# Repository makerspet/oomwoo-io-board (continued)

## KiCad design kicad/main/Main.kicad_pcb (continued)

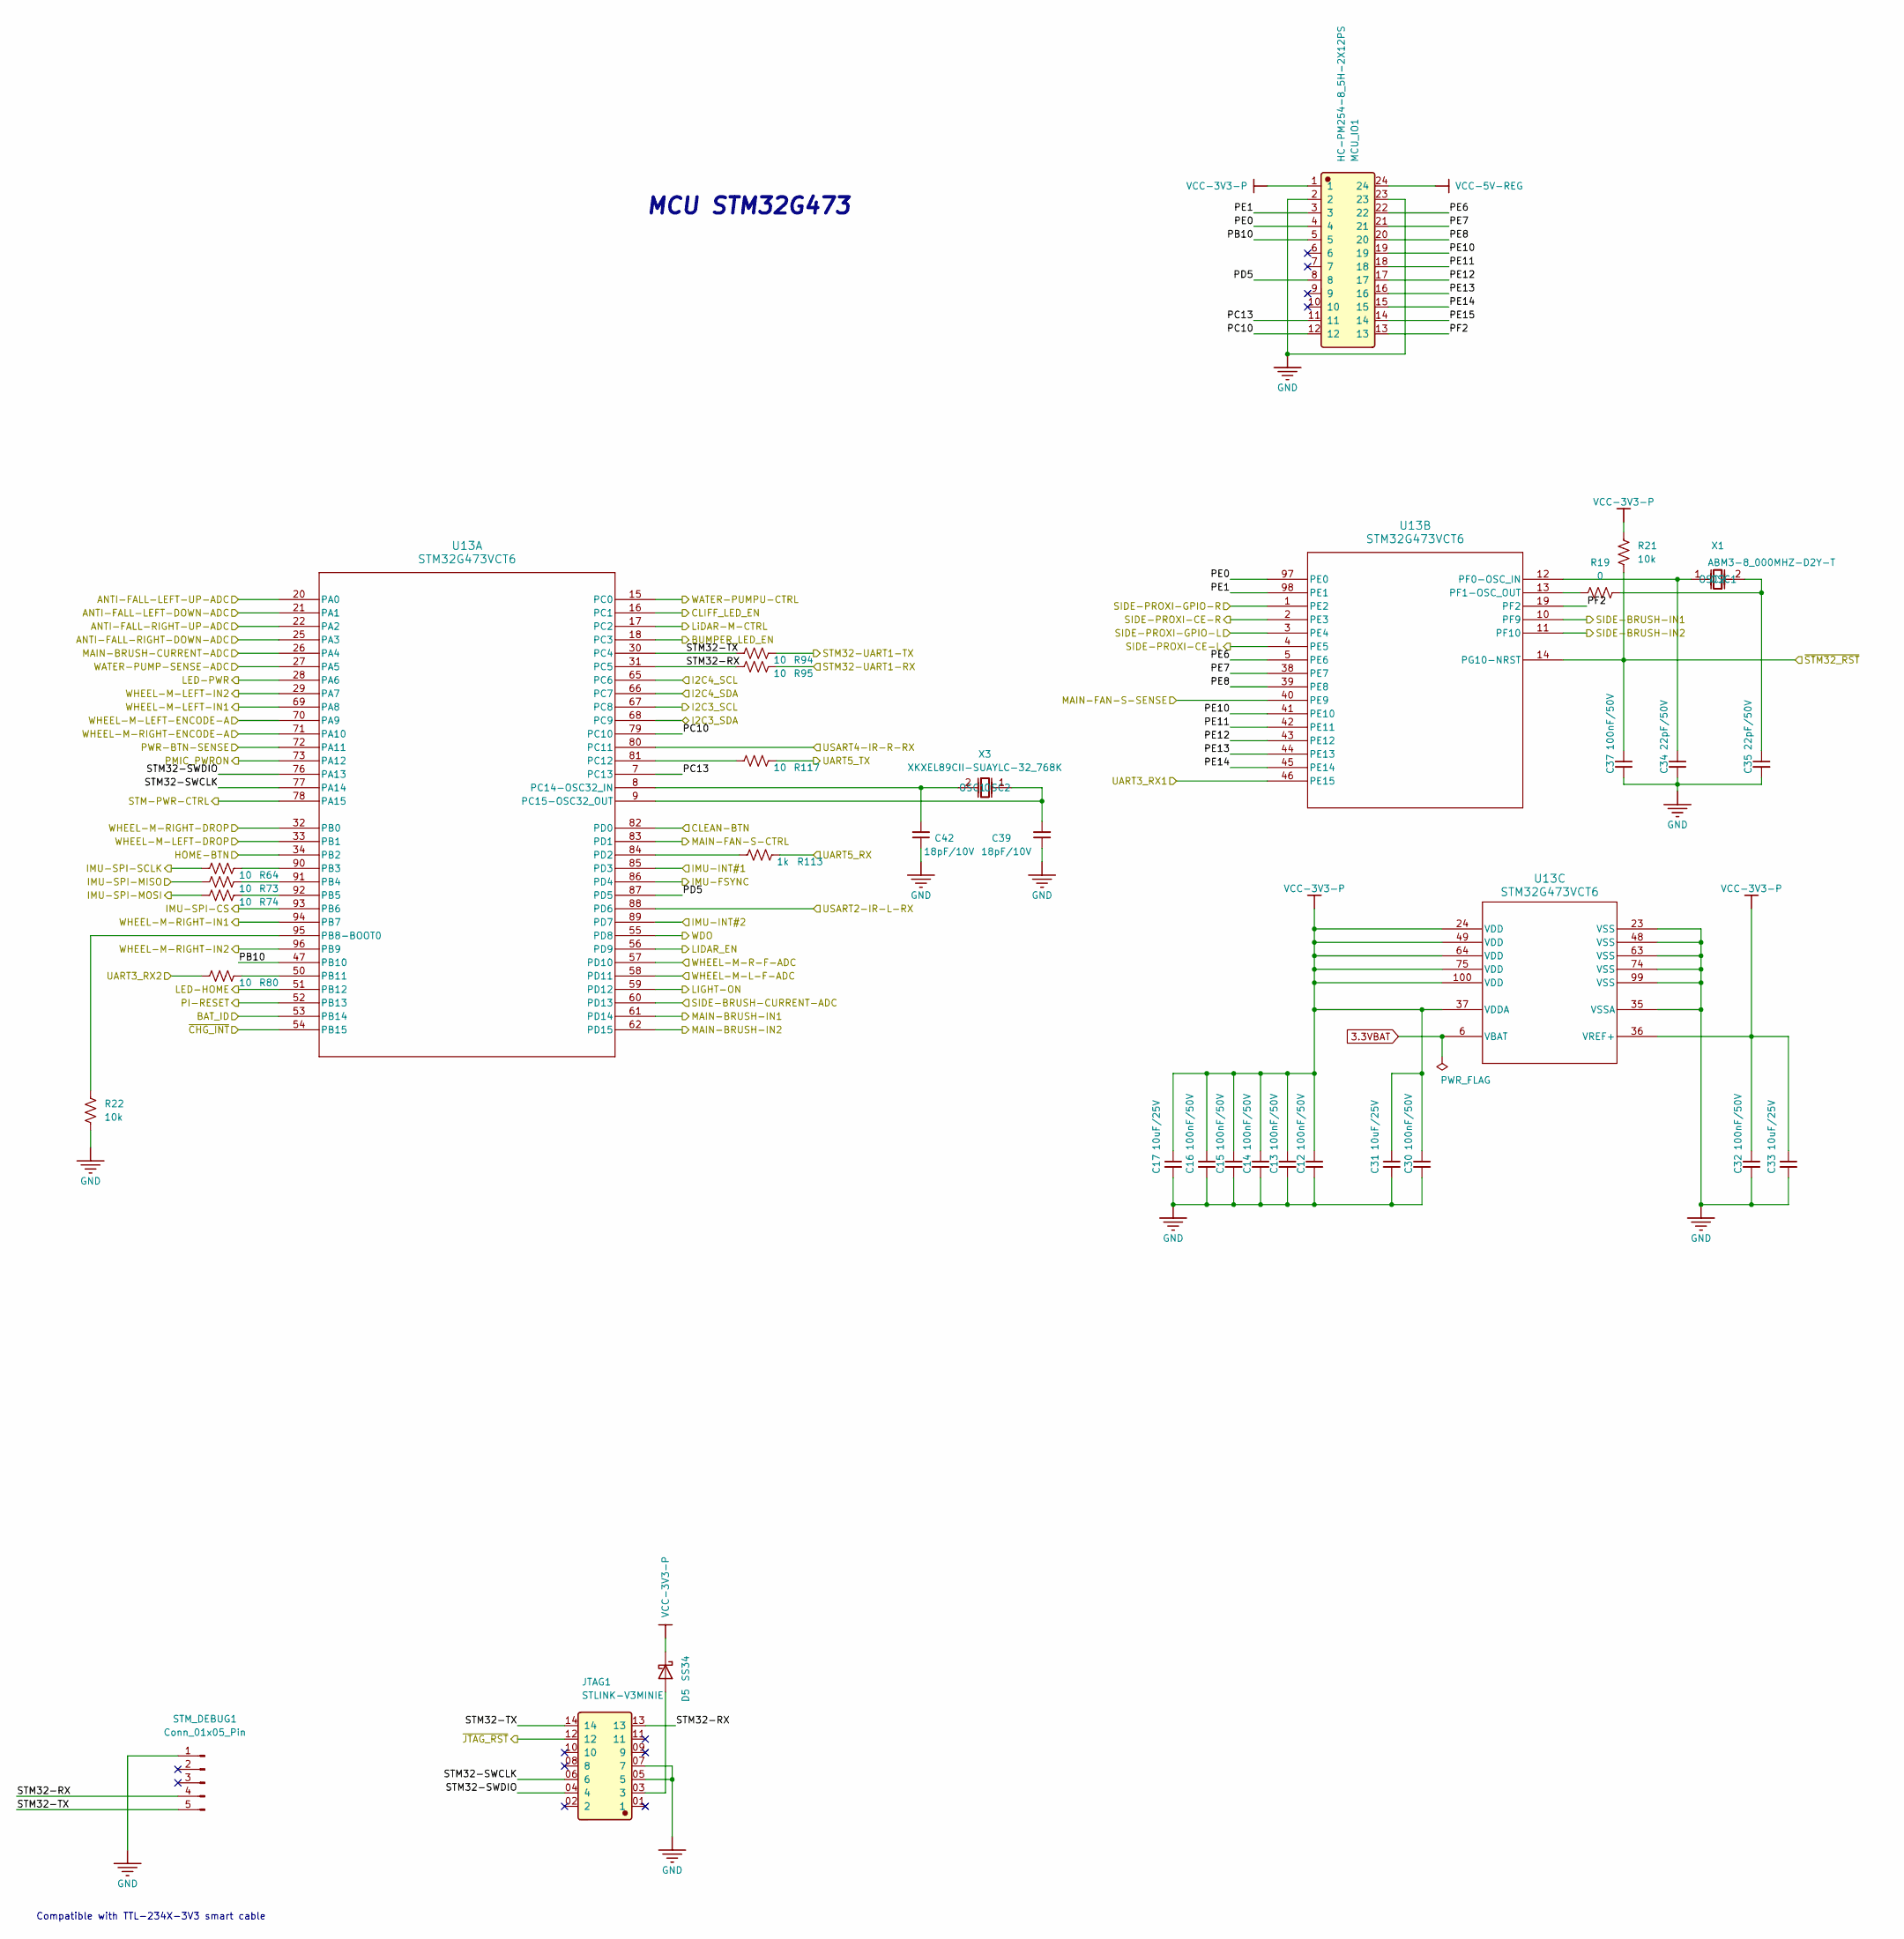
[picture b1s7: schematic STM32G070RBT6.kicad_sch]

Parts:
C12, C13, C14, C15, C16, C30, C32, C37: 100nF/50V; C_0603_1608Metric; LCSC C1591
C17, C31, C33: 10uF/25V; C_0603_1608Metric; LCSC C96446
C34, C35: 22pF/50V; C_0603_1608Metric
C39, C42: 18pF/10V; C_0603_1608Metric
D5: SS34; D_SMA; LCSC C22448055
JTAG1: STLINK-V3MINIE; FTSH-107-01-L-DV-K-A; Manufacturer Part FTSH-107-01-L-DV-K-A; LCSC C5563894
MCU_IO1: HC-PM254-8_5H-2X12PS; Manufacturer Part HC-PM254-8.5H-2x12PS; LCSC C22436159
R19: 0; R_0603_1608Metric
R21, R22: 10k; R_0603_1608Metric
R64, R73, R74, R80, R94, R95, R117: 10; R_0603_1608Metric
R113: 1k; R_0603_1608Metric
STM_DEBUG1: Conn_01x05_Pin; PinHeader_1x05_P2.54mm_Vertical; LCSC C42431835
U13: STM32G473VCT6; LQFP100-14x14mm; LCSC C730121
X1: ABM3-8_000MHZ-D2Y-T; Manufacturer Part ABM3-8.000MHZ-D2Y-T; LCSC C144380
X3: XKXEL89CII-SUAYLC-32_768K; Manufacturer Part XKXEL89CII-SUAYLC-32.768K; LCSC C18214309

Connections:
3.3VBAT: U13.6 (VBAT); also elsewhere on the board
/ANTI-FALL/ANTI-FALL-LEFT-DOWN-ADC: U13.21 (PA1); also elsewhere on the board
/ANTI-FALL/ANTI-FALL-LEFT-UP-ADC: U13.20 (PA0); also elsewhere on the board
/ANTI-FALL/ANTI-FALL-RIGHT-DOWN-ADC: U13.25 (PA3); also elsewhere on the board
/ANTI-FALL/ANTI-FALL-RIGHT-UP-ADC: U13.22 (PA2); also elsewhere on the board
/ANTI-FALL/BUMPER_LED_EN: U13.18 (PC3); also elsewhere on the board
/ANTI-FALL/CLIFF_LED_EN: U13.16 (PC1); also elsewhere on the board
/BATTERY-CHARGER/ID: U13.53 (PB14); also elsewhere on the board
/BATTERY-CHARGER/SCL: U13.67 (PC8); also elsewhere on the board
/BATTERY-CHARGER/SDA: U13.68 (PC9); also elsewhere on the board
/BATTERY-CHARGER/~INT: U13.54 (PB15); also elsewhere on the board
/BUTTON-LED/CLEAN-BTN: U13.82 (PD0); also elsewhere on the board
/BUTTON-LED/HOME-BTN: U13.34 (PB2); also elsewhere on the board
/BUTTON-LED/LED-HOME: U13.51 (PB12); also elsewhere on the board
/BUTTON-LED/LED-PWR: U13.28 (PA6); also elsewhere on the board
/CM5-GPIO/PMIC_EN: U13.52 (PB13); also elsewhere on the board
/CM5-GPIO/RUN_PG: U13.73 (PA12); also elsewhere on the board
/CM5-GPIO/UART2_RX: R94.2; also elsewhere on the board
/CM5-GPIO/UART2_TX: R95.2; also elsewhere on the board
/FRONT SENSORS/IR-F-RX1: U13.46 (PE15); also elsewhere on the board
/FRONT SENSORS/IR-F-RX2: R80.1; also elsewhere on the board
/FRONT SENSORS/LIGHT-ON: U13.59 (PD12); also elsewhere on the board
/IMU-CS: U13.93 (PB6); also elsewhere on the board
/IMU-FSYNC: U13.86 (PD4); also elsewhere on the board
/IMU-INT1: U13.85 (PD3); also elsewhere on the board
/IMU-INT2: U13.89 (PD7); also elsewhere on the board
/IMU-MISO: R73.1; also elsewhere on the board
/IMU-MOSI: R74.1; also elsewhere on the board
/IMU-SCLK: R64.1; also elsewhere on the board
/LiDAR/LIDAR_EN: U13.56 (PD9); also elsewhere on the board
/LiDAR/LiDAR-MOTOR-CTRL: U13.17 (PC2); also elsewhere on the board
/LiDAR/LiDAR-RXD: R113.2; also elsewhere on the board
/LiDAR/LiDAR-TXD: R117.2; also elsewhere on the board
/MAIN-BRUSH MOTOR/MAIN-BRUSH-CURRENT-ADC: U13.26 (PA4); also elsewhere on the board
/MAIN-BRUSH MOTOR/MAIN-BRUSH-IN1: U13.61 (PD14); also elsewhere on the board
/MAIN-BRUSH MOTOR/MAIN-BRUSH-IN2: U13.62 (PD15); also elsewhere on the board
/MAIN-FAN/MAIN-FAN-S-CTRL: U13.83 (PD1); also elsewhere on the board
/MAIN-FAN/MAIN-FAN-S-SENSE: U13.40 (PE9); also elsewhere on the board
/MCU-STM32/I2C4_SCL: U13.65 (PC6); also elsewhere on the board
/MCU-STM32/I2C4_SDA: U13.66 (PC7); also elsewhere on the board
/MCU-STM32/PB10: MCU_IO1.5, U13.47 (PB10)
/MCU-STM32/PC10: MCU_IO1.12, U13.79 (PC10)
/MCU-STM32/PC13: MCU_IO1.11, U13.7 (PC13)
/MCU-STM32/PD5: MCU_IO1.8, U13.87 (PD5)
/MCU-STM32/PE0: MCU_IO1.4, U13.97 (PE0)
/MCU-STM32/PE1: MCU_IO1.3, U13.98 (PE1)
/MCU-STM32/PE6: MCU_IO1.22, U13.5 (PE6)
/MCU-STM32/PE7: MCU_IO1.21, U13.38 (PE7)
/MCU-STM32/PE8: MCU_IO1.20, U13.39 (PE8)
/MCU-STM32/PE10: MCU_IO1.19, U13.41 (PE10)
/MCU-STM32/PE11: MCU_IO1.18, U13.42 (PE11)
/MCU-STM32/PE12: MCU_IO1.17, U13.43 (PE12)
/MCU-STM32/PE13: MCU_IO1.16, U13.44 (PE13)
/MCU-STM32/PE14: MCU_IO1.15, U13.45 (PE14)
/MCU-STM32/PE15: MCU_IO1.14
/MCU-STM32/PF2: MCU_IO1.13, U13.19 (PF2)
/MCU-STM32/PWR-BTN-SENSE: U13.72 (PA11); also elsewhere on the board
/MCU-STM32/SIDE-BRUSH-CURRENT-ADC: U13.60 (PD13); also elsewhere on the board
/MCU-STM32/SIDE-BRUSH-IN1: U13.10 (PF9); also elsewhere on the board
/MCU-STM32/SIDE-BRUSH-IN2: U13.11 (PF10); also elsewhere on the board
/MCU-STM32/SIDE-PROXI-CE-L: U13.4 (PE5); also elsewhere on the board
/MCU-STM32/SIDE-PROXI-CE-R: U13.2 (PE3); also elsewhere on the board
/MCU-STM32/SIDE-PROXI-GPIO-L: U13.3 (PE4); also elsewhere on the board
/MCU-STM32/SIDE-PROXI-GPIO-R: U13.1 (PE2); also elsewhere on the board
/MCU-STM32/STM32-RX: JTAG1.13, R95.1, STM_DEBUG1.4, U13.31 (PC5)
/MCU-STM32/STM32-SWCLK: JTAG1.06 (6), U13.77 (PA14)
/MCU-STM32/STM32-SWDIO: JTAG1.04 (4), U13.76 (PA13)
/MCU-STM32/STM32-TX: JTAG1.14, R94.1, STM_DEBUG1.5, U13.30 (PC4)
/MCU-STM32/STM-PWR-CTRL: U13.78 (PA15); also elsewhere on the board
/MCU-STM32/USART2-IR-L-RX: U13.88 (PD6); also elsewhere on the board
/MCU-STM32/USART4-IR-R-RX: U13.80 (PC11); also elsewhere on the board
/MCU-STM32/WATER-PUMP-SENSE-ADC: U13.27 (PA5); also elsewhere on the board
/MCU-STM32/WATER-PUMPU-CTRL: U13.15 (PC0); also elsewhere on the board
/MCU-STM32/WDO: U13.55 (PD8); also elsewhere on the board
/MCU-STM32/WHEEL-M-L-F-ADC: U13.58 (PD11); also elsewhere on the board
/MCU-STM32/WHEEL-M-LEFT-DROP: U13.33 (PB1); also elsewhere on the board
/MCU-STM32/WHEEL-M-LEFT-ENCODE-A: U13.70 (PA9); also elsewhere on the board
/MCU-STM32/WHEEL-M-LEFT-IN1: U13.69 (PA8); also elsewhere on the board
/MCU-STM32/WHEEL-M-LEFT-IN2: U13.29 (PA7); also elsewhere on the board
/MCU-STM32/WHEEL-M-R-F-ADC: U13.57 (PD10); also elsewhere on the board
/MCU-STM32/WHEEL-M-RIGHT-DROP: U13.32 (PB0); also elsewhere on the board
/MCU-STM32/WHEEL-M-RIGHT-ENCODE-A: U13.71 (PA10); also elsewhere on the board
/MCU-STM32/WHEEL-M-RIGHT-IN1: U13.94 (PB7); also elsewhere on the board
/MCU-STM32/WHEEL-M-RIGHT-IN2: U13.96 (PB9); also elsewhere on the board
/MCU-STM32/~JTAG_RST: JTAG1.12; also elsewhere on the board
/MCU-STM32/~STM32_RST: C37.1, R21.1, U13.14 (PG10-NRST); also elsewhere on the board
GND: C12.2, C13.2, C14.2, C15.2, C16.2, C17.2, C30.2, C31.2, C32.2, C33.2, C34.2, C35.2, C37.2, C39.1, C42.1, JTAG1.05 (5), JTAG1.07 (7), MCU_IO1.2, MCU_IO1.23, R22.1, STM_DEBUG1.1, U13.23 (VSS), U13.35 (VSSA), U13.48 (VSS), U13.63 (VSS), U13.74 (VSS), U13.99 (VSS); also elsewhere on the board
unnamed: D5.2 (A), JTAG1.03 (3)
unnamed: R64.2, U13.90 (PB3)
unnamed: R73.2, U13.91 (PB4)
unnamed: R74.2, U13.92 (PB5)
unnamed: R22.2, U13.95 (PB8-BOOT0)
unnamed: R80.2, U13.50 (PB11)
unnamed: R117.1, U13.81 (PC12)
unnamed: C42.2, U13.8 (PC14-OSC32_IN), X3.2 (OSC2)
unnamed: C39.2, U13.9 (PC15-OSC32_OUT), X3.1 (OSC1)
unnamed: R113.1, U13.84 (PD2)
unnamed: C34.1, U13.12 (PF0-OSC_IN), X1.1 (OSC1)
unnamed: R19.1, U13.13 (PF1-OSC_OUT)
unnamed: C35.1, R19.2, X1.2 (OSC2)
VCC-3V3-P: C12.1, C13.1, C14.1, C15.1, C16.1, C17.1, C30.1, C31.1, C32.1, C33.1, D5.1 (K), MCU_IO1.1, R21.2, U13.24 (VDD), U13.36 (VREF+), U13.37 (VDDA), U13.49 (VDD), U13.64 (VDD), U13.75 (VDD), U13.100 (VDD); also elsewhere on the board
VCC-5V-REG: MCU_IO1.24; also elsewhere on the board

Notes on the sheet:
Compatible with TTL-234X-3V3 smart cable
MCU STM32G473

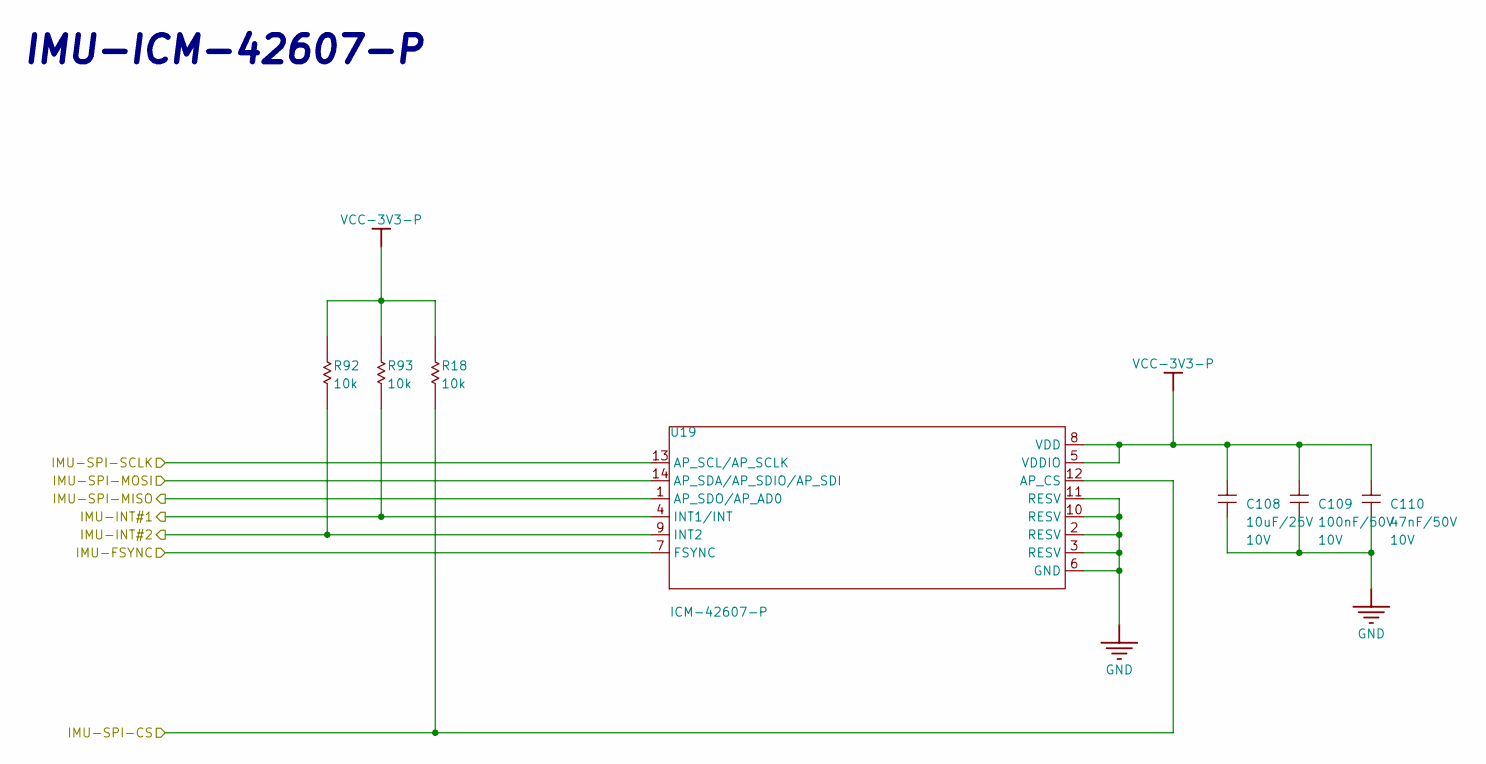
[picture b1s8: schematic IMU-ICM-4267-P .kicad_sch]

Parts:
C108: 10uF/25V; C_0603_1608Metric; VOLTAGERATE 10V; MANUFACTURINGPARTNUMBER *; LCSC C96446
C109: 100nF/50V; C_0603_1608Metric; VOLTAGERATE 10V; MANUFACTURINGPARTNUMBER *; LCSC C1591
C110: 47nF/50V; C_0603_1608Metric; VOLTAGERATE 10V; MANUFACTURINGPARTNUMBER *
R18, R92, R93: 10k; R_0603_1608Metric; VOLTAGERATE *; MANUFACTURINGPARTNUMBER *
U19: ICM-42607-P; VOLTAGERATE *; MANUFACTURINGPARTNUMBER *; LCSC C5129967

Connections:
/IMU-CS: R18.2, U19.12 (AP_CS); also elsewhere on the board
/IMU-FSYNC: U19.7 (FSYNC); also elsewhere on the board
/IMU-INT1: R93.2, U19.4 (INT1/INT); also elsewhere on the board
/IMU-INT2: R92.2, U19.9 (INT2); also elsewhere on the board
/IMU-MISO: U19.1 (AP_SDO/AP_AD0); also elsewhere on the board
/IMU-MOSI: U19.14 (AP_SDA/AP_SDIO/AP_SDI); also elsewhere on the board
/IMU-SCLK: U19.13 (AP_SCL/AP_SCLK); also elsewhere on the board
GND: C108.1, C109.1, C110.1, U19.2 (RESV), U19.3 (RESV), U19.6 (GND), U19.10 (RESV), U19.11 (RESV); also elsewhere on the board
VCC-3V3-P: C108.2, C109.2, C110.2, R18.1, R92.1, R93.1, U19.5 (VDDIO), U19.8 (VDD); also elsewhere on the board

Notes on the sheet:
IMU-ICM-42607-P

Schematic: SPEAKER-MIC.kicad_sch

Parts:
C5, C9, C10: 100nF/50V; C_0603_1608Metric; LCSC C1591
C11: 10uF/25V; C_0603_1608Metric; LCSC C96446
ED3: ESD5451N; ESD0402; PART REFERENCE ED7010; LCSC C5261080
ED4: ESD5451N; ESD0402; PART REFERENCE ED7011; LCSC C5261080
Q9: 2302V; Manufacturer Part 2302V; LCSC C7431443
R8, R13: 100k; R_0603_1608Metric
R9, R12: 0; R_0603_1608Metric
SPK1: ZX-ZH1_5-2PWT; Manufacturer Part ZX-ZH1.5-2PWT; LCSC C19272405
U9, U10: ICS-43434_C5656610; Manufacturer Part ICS-43434; LCSC C5656610
U11: MAX98357AETE_T; Manufacturer Part MAX98357AETE+T; LCSC C910544

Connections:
+3.3VP: R13.1; also elsewhere on the board
/CM5-GPIO/GPIO06: Q9.1 (G), R13.2; also elsewhere on the board
/CM5-GPIO/I2S_DOUT: U11.1 (DIN); also elsewhere on the board
/SPEAKER-MIC/BCLK: U9.4 (SCK), U10.4 (SCK), U11.16 (BCLK); also elsewhere on the board
/SPEAKER-MIC/DOUT: R8.1, U9.6 (SD), U10.6 (SD); also elsewhere on the board
/SPEAKER-MIC/LRCLK: U9.1 (WS), U10.1 (WS), U11.14 (LRCLK); also elsewhere on the board
GND: C5.2, C9.2, C10.2, C11.2, ED3.2, ED4.2, Q9.2 (S), R8.2, R12.1, SPK1.3, SPK1.4, U9.2 (LR), U9.3 (GND), U10.3 (GND), U11.3 (GND), U11.11 (GND), U11.15 (GND), U11.17 (EP); also elsewhere on the board
unnamed: Q9.3 (D), R9.1
unnamed: R12.2, U11.2 (GAIN_SLOT)
unnamed: ED3.1, SPK1.2, U11.10 (OUTN)
unnamed: ED4.1, SPK1.1, U11.9 (OUTP)
unnamed: R9.2, U11.4 (SD_MODE#)
VCC-3V3-P: C5.1, C9.1, U9.5 (VDD), U10.2 (LR), U10.5 (VDD); also elsewhere on the board
VCC-5V-REG: C10.1, C11.1, U11.7 (VDD), U11.8 (VDD); also elsewhere on the board

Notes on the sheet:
Microphone Input
RIGHT CHANNEL SELECT
SPEAKER MIC
LEFT CHANNEL SELECT
12dB

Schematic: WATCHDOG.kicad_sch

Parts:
C56: 100nF/50V; C_0603_1608Metric; Part Description 0.1uF 10% 16V Ceramic Capacitor X7R 040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; LCSC C1591
R135: 100k; R_0603_1608Metric
U2: TPS3828-33DBVR; Manufacturer Part TPS3828-33DBVR; LCSC C20032

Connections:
/MCU-STM32/WDO: U2.4 (WDI); also elsewhere on the board
/MCU-STM32/~JTAG_RST: R135.2, U2.3 (MR#); also elsewhere on the board
/MCU-STM32/~STM32_RST: U2.1 (RESET#); also elsewhere on the board
GND: C56.2, U2.2 (GND); also elsewhere on the board
VCC-3V3-P: C56.1, R135.1, U2.5 (VDD); also elsewhere on the board

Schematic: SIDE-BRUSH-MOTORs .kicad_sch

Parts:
C92: 100nF/50V; C_0603_1608Metric; VOLTAGERATE 50V; MANUFACTURINGPARTNUMBER *; LCSC C1591
C138: 10uF/25V; C_0603_1608Metric; LCSC C96446
D22: 1N4007; SOD123; VOLTAGERATE *; MANUFACTURINGPARTNUMBER *; LCSC C2892681
R55, R57: 100k; R_0603_1608Metric
R88: 0.2R/10W; R_2512_6332Metric; VOLTAGERATE *; MANUFACTURINGPARTNUMBER *; LCSC C5375488
R110: 10k; R_0603_1608Metric; VOLTAGERATE *; MANUFACTURINGPARTNUMBER *
SIDE_BRUSH1: ZX-ZH1_5-2PWT; Manufacturer Part ZX-ZH1.5-2PWT; LCSC C19272405
U18: DRV8870DDAR; VOLTAGERATE *; MANUFACTURINGPARTNUMBER *; LCSC C86590

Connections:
/MCU-STM32/SIDE-BRUSH-CURRENT-ADC: D22.1 (A), R110.1; also elsewhere on the board
/MCU-STM32/SIDE-BRUSH-IN1: R55.1, U18.3 (IN1); also elsewhere on the board
/MCU-STM32/SIDE-BRUSH-IN2: R57.1, U18.2 (IN2); also elsewhere on the board
GND: C92.1, C138.2, D22.2 (K), R55.2, R57.2, R88.1, SIDE_BRUSH1.3, SIDE_BRUSH1.4, U18.1 (GND), U18.9 (EP); also elsewhere on the board
unnamed: R88.2, R110.2, U18.7 (ISEN)
unnamed: SIDE_BRUSH1.1, U18.6 (OUT1)
unnamed: SIDE_BRUSH1.2, U18.8 (OUT2)
VCC-3V3-P: U18.4 (VREF); also elsewhere on the board
VM-VBAT: C92.2, C138.1, U18.5 (VM); also elsewhere on the board

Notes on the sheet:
SIDE-BRUSH MOTOR CONTROL

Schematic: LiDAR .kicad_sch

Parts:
C139: 10uF/25V; C_0603_1608Metric; LCSC C96446
D10: SS34; D_SMA; VOLTAGERATE *; MANUFACTURINGPARTNUMBER *; LCSC C22448055
Q20: AO3400; SOT23-3D; VOLTAGERATE *; MANUFACTURINGPARTNUMBER *; LCSC C20628874
R65: 1k; R_0603_1608Metric
R116, R118: 100k; R_0603_1608Metric; VOLTAGERATE *; MANUFACTURINGPARTNUMBER *
U3: HC-PM254-5_0H-2X4PS-02A; Manufacturer Part HC-PM254-5.0H-2x4PS-02A; LCSC C42163132

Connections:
/LiDAR/LIDAR_EN: R118.2, U3.6; also elsewhere on the board
/LiDAR/LiDAR-MOTOR-CTRL: Q20.1 (G), R116.2, U3.8; also elsewhere on the board
/LiDAR/LiDAR-RXD: R65.1; also elsewhere on the board
/LiDAR/LiDAR-TXD: U3.5; also elsewhere on the board
GND: C139.2, Q20.2 (S), R116.1, R118.1, U3.7; also elsewhere on the board
unnamed: D10.1 (A), Q20.3 (D), U3.4
unnamed: R65.2, U3.3
VCC-5V-REG: C139.1, D10.2 (K), U3.1, U3.2; also elsewhere on the board

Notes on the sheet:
LiDAR

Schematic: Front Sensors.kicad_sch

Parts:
C6, C19, C90, C91, C123: 10uF/25V; C_0603_1608Metric; LCSC C96446
IR-F1, IR-F2: ZX-ZH1_5-4PWT; Manufacturer Part ZX-ZH1.5-4PWT; LCSC C19272407
LIGHT1: ZX-ZH1_5-2PWT; Manufacturer Part ZX-ZH1.5-2PWT; LCSC C19272405
Q2: 2302V; Manufacturer Part 2302V; LCSC C7431443
R2, R7, R61, R62: 47k; R_0603_1608Metric
R5, R6: 2.2k; R_0603_1608Metric
R54: 100k; R_0603_1608Metric
VL-L1: ZX-ZH1_5-7PWT; Manufacturer Part ZX-ZH1.5-7PWT; LCSC C19272410
VL-R1: ZX-ZH1_5-7PWT; Manufacturer Part ZX-ZH1.5-7PWT; LCSC C19272410

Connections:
/CM5-GPIO/GPIO16: VL-R1.7; also elsewhere on the board
/CM5-GPIO/GPIO17: R2.1, VL-L1.3, VL-R1.3; also elsewhere on the board
/CM5-GPIO/GPIO25: R61.2, VL-L1.6; also elsewhere on the board
/CM5-GPIO/GPIO26: R62.2, VL-L1.7; also elsewhere on the board
/CM5-GPIO/GPIO27: R7.2, VL-R1.6; also elsewhere on the board
/CM5-GPIO/SCL1: R6.2, VL-L1.5, VL-R1.5; also elsewhere on the board
/CM5-GPIO/SDA1: R5.2, VL-L1.4, VL-R1.4; also elsewhere on the board
/FRONT SENSORS/IR-F-RX1: IR-F1.4; also elsewhere on the board
/FRONT SENSORS/IR-F-RX2: IR-F2.4; also elsewhere on the board
/FRONT SENSORS/LIGHT-ON: Q2.1 (G), R54.1; also elsewhere on the board
GND: C6.2, C19.2, C90.2, C91.2, C123.2, IR-F1.2, IR-F1.3, IR-F1.5, IR-F1.6, IR-F2.2, IR-F2.3, IR-F2.5, IR-F2.6, LIGHT1.3, LIGHT1.4, Q2.2 (S), R2.2, R54.2, VL-L1.2, VL-L1.8, VL-L1.9, VL-R1.2, VL-R1.8, VL-R1.9; also elsewhere on the board
unnamed: C6.1, VL-L1.1
unnamed: C123.1, LIGHT1.2, Q2.3 (D)
VCC-3V3-P: C19.1, C90.1, C91.1, IR-F1.1, IR-F2.1, LIGHT1.1, R5.1, R6.1, R7.1, R61.1, R62.1, VL-R1.1; also elsewhere on the board

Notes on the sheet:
SCL
VDD
LPn
I2C-RST
IR LIGHT
SDA
RECEIVER
INT
https://thepihut.com/products/850nm-ir-led-modules?srsltid=AfmBOorZ0hl4HylQHd5JbNfaA7bqJMbzrmY0bn7Mm12pD_mKEoiRE0nX
GND
2 IR RECEIVERS
2x VL53L7CX

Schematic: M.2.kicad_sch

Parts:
C45: 10uF/25V; C_0603_1608Metric; Manufacturer_Part_Number GRM21BR61H106KE43L; LCSC C96446
C50: 100nF/50V; C_0603_1608Metric; Manufacturer_Part_Number CL10B104KB8NNNC; LCSC C1591
J2: 1-2199119-5; TE_1-2199119-5; LCSC C574849
M2_ACT1: YLED0603B; Manufacturer Part YLED0603B; LCSC C19171394
MP1, MP2, MP3, MP4: M3 x 1.5mm; MountingHole_3.2mm_M3_Pad; PART-NUMBER 9774015360R
R79: 1k; R_0603_1608Metric
Y1: ASEK-32.768KHZ-LRT; XTAL_ASEK-32.768KHZ-LRT; PARTREV 01-11-22; LCSC C2650753

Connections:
/CM5-HIGHSPEED/PCIE_CLK_N: J2.53; also elsewhere on the board
/CM5-HIGHSPEED/PCIE_CLK_P: J2.55; also elsewhere on the board
/CM5-HIGHSPEED/PCIE_CLK_nREQ: J2.52; also elsewhere on the board
/CM5-HIGHSPEED/PCIE_RX_N: J2.43; also elsewhere on the board
/CM5-HIGHSPEED/PCIE_RX_P: J2.41; also elsewhere on the board
/CM5-HIGHSPEED/PCIE_TX_N: J2.49; also elsewhere on the board
/CM5-HIGHSPEED/PCIE_TX_P: J2.47; also elsewhere on the board
/CM5-HIGHSPEED/PCIE_nRST: J2.50; also elsewhere on the board
/CM5-HIGHSPEED/PCIE_nWAKE: J2.54; also elsewhere on the board
GND: C45.2, C50.2, J2.1, J2.3, J2.9, J2.15, J2.21, J2.27, J2.33, J2.39, J2.45, J2.51, J2.57, J2.71, J2.73, J2.75, J2.SH1 (SHIELD), J2.SH2 (SHIELD), MP1.1, MP2.1, MP3.1, MP4.1, Y1.2 (GND/CASE); also elsewhere on the board
unnamed: J2.10, M2_ACT1.2 (K)
unnamed: J2.68, Y1.3 (OUTPUT)
unnamed: M2_ACT1.1 (A), R79.2
VCC3V3_M2: C45.1, C50.1, J2.2, J2.4, J2.12, J2.14, J2.16, J2.18, J2.70, J2.72, J2.74, R79.1, Y1.1 (TRI-STATE), Y1.4 (VDD); also elsewhere on the board

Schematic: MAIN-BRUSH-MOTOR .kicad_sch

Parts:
C103: 100nF/50V; C_0603_1608Metric; VOLTAGERATE 50V; MANUFACTURINGPARTNUMBER *; LCSC C1591
C134: 10uF/25V; C_0603_1608Metric; LCSC C96446
MAIN_BRUSH1: ZX-ZH1_5-2PWT; Manufacturer Part ZX-ZH1.5-2PWT; LCSC C19272405
R3, R4: 100k; R_0603_1608Metric
R112: 0.2R/10W; R_2512_6332Metric; VOLTAGERATE *; MANUFACTURINGPARTNUMBER *; LCSC C5375488
U20: DRV8870DDAR; VOLTAGERATE *; MANUFACTURINGPARTNUMBER *; LCSC C86590

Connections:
/MAIN-BRUSH MOTOR/MAIN-BRUSH-CURRENT-ADC: R112.2, U20.7 (ISEN); also elsewhere on the board
/MAIN-BRUSH MOTOR/MAIN-BRUSH-IN1: R3.1, U20.3 (IN1); also elsewhere on the board
/MAIN-BRUSH MOTOR/MAIN-BRUSH-IN2: R4.1, U20.2 (IN2); also elsewhere on the board
GND: C103.1, C134.2, MAIN_BRUSH1.3, MAIN_BRUSH1.4, R3.2, R4.2, R112.1, U20.1 (GND), U20.9 (EP); also elsewhere on the board
unnamed: MAIN_BRUSH1.1, U20.6 (OUT1)
unnamed: MAIN_BRUSH1.2, U20.8 (OUT2)
VCC-3V3-P: U20.4 (VREF); also elsewhere on the board
VM-VBAT: C103.2, C134.1, U20.5 (VM); also elsewhere on the board

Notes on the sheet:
MAIN BUSH MOTOR CONTROL

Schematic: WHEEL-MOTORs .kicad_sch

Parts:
C84, C88: 100nF/50V; C_0603_1608Metric; VOLTAGERATE 50V; MANUFACTURINGPARTNUMBER *; LCSC C1591
C135, C136: 10uF/25V; C_0603_1608Metric; LCSC C96446
C142, C143: 100nF/50V; C_0603_1608Metric; Manufacturer_Part_Number CL10B104KB8NNNC; LCSC C1591
MOT_WHEEL_L1: ZX-ZH1_5-7PWT; Manufacturer Part ZX-ZH1.5-7PWT; LCSC C19272410
MOT_WHEEL_R1: ZX-ZH1_5-7PWT; Manufacturer Part ZX-ZH1.5-7PWT; LCSC C19272410
R11, R17, R20, R27: 100k; R_0603_1608Metric
R49, R50, R51, R52: 10k; R_0603_1608Metric
R83, R84: 0.2R/10W; R_2512_6332Metric; VOLTAGERATE *; MANUFACTURINGPARTNUMBER *; LCSC C5375488
U14, U15: DRV8870DDAR; VOLTAGERATE *; MANUFACTURINGPARTNUMBER *; LCSC C86590

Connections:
/MCU-STM32/WHEEL-M-L-F-ADC: R84.2, U15.7 (ISEN); also elsewhere on the board
/MCU-STM32/WHEEL-M-LEFT-DROP: MOT_WHEEL_L1.7, R50.2; also elsewhere on the board
/MCU-STM32/WHEEL-M-LEFT-ENCODE-A: MOT_WHEEL_L1.4, R52.2; also elsewhere on the board
/MCU-STM32/WHEEL-M-LEFT-IN1: R20.1, U15.3 (IN1); also elsewhere on the board
/MCU-STM32/WHEEL-M-LEFT-IN2: R27.1, U15.2 (IN2); also elsewhere on the board
/MCU-STM32/WHEEL-M-R-F-ADC: R83.2, U14.7 (ISEN); also elsewhere on the board
/MCU-STM32/WHEEL-M-RIGHT-DROP: MOT_WHEEL_R1.7, R49.2; also elsewhere on the board
/MCU-STM32/WHEEL-M-RIGHT-ENCODE-A: MOT_WHEEL_R1.4, R51.2; also elsewhere on the board
/MCU-STM32/WHEEL-M-RIGHT-IN1: R11.1, U14.3 (IN1); also elsewhere on the board
/MCU-STM32/WHEEL-M-RIGHT-IN2: R17.1, U14.2 (IN2); also elsewhere on the board
GND: C84.1, C88.1, C135.2, C136.2, C142.2, C143.2, MOT_WHEEL_L1.3, MOT_WHEEL_L1.6, MOT_WHEEL_L1.8, MOT_WHEEL_L1.9, MOT_WHEEL_R1.3, MOT_WHEEL_R1.6, MOT_WHEEL_R1.8, MOT_WHEEL_R1.9, R11.2, R17.2, R20.2, R27.2, R83.1, R84.1, U14.1 (GND), U14.9 (EP), U15.1 (GND), U15.9 (EP); also elsewhere on the board
unnamed: MOT_WHEEL_R1.1, U14.6 (OUT1)
unnamed: MOT_WHEEL_R1.2, U14.8 (OUT2)
unnamed: MOT_WHEEL_L1.1, U15.6 (OUT1)
unnamed: MOT_WHEEL_L1.2, U15.8 (OUT2)
VCC-3V3-P: C142.1, C143.1, MOT_WHEEL_L1.5, MOT_WHEEL_R1.5, R49.1, R50.1, R51.1, R52.1, U14.4 (VREF), U15.4 (VREF); also elsewhere on the board
VM-VBAT: C84.2, C88.2, C135.1, C136.1, U14.5 (VM), U15.5 (VM); also elsewhere on the board

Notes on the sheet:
WHEEL MOTOR CONTROL

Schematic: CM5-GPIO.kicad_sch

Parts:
BOOT1: Conn_01x02_Pin; PinHeader_1x02_P2.54mm_Vertical; LCSC C32713268
C1, C2, C4: 100nF/50V; C_0603_1608Metric; Part Description 0.1uF 10% 16V Ceramic Capacitor X7R 040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; LCSC C1591
C3: 10uF/25V; C_0603_1608Metric; Part Description 10uF 10% 10V Ceramic Capacitor X7R 0805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; LCSC C96446
CM_ACT1: YLED0603B; Manufacturer Part YLED0603B; LCSC C19171394
CM_PWR1: YLED0603B; Manufacturer Part YLED0603B; LCSC C19171394
CONSOLE1: Conn_01x05_Pin; PinHeader_1x05_P2.54mm_Vertical; LCSC C42431835
H1: PM254-2-06-S-8_5; Manufacturer Part PM254-2-06-S-8.5; LCSC C3975151
Module1: ComputeModule5-CM5; Raspberry-Pi-5-Compute-Module; Part Description 100 Position Connector Receptacle, Cent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; LCSC 2X C6932320
Q10: 2302V; Manufacturer Part 2302V; LCSC C7431443
R82, R85: 1k; R_0603_1608Metric
R142: 10k; R_0603_1608Metric
SDCARD2: 1040310811; Manufacturer Part 1040310811; LCSC C585350
U6: RT9742GGJ5; Manufacturer Part RT9742GGJ5; LCSC C250547

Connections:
+3.3VP: C1.1, Module1.78 (GPIO_VREF(1.8v/3.3v_Input)), Module1.84 (+3.3v_(Output)), Module1.86 (+3.3v_(Output)), R82.1, R85.1, R142.1, U6.5 (VIN); also elsewhere on the board
/CAMERA/CAM_GPIO0: Module1.100 (CAM_GPIO1); also elsewhere on the board
/CAMERA/CAM_GPIO1: Module1.97 (CAM_GPIO0); also elsewhere on the board
/CAMERA/ID_SC: Module1.35 (ID_SC); also elsewhere on the board
/CAMERA/ID_SD: Module1.36 (ID_SD); also elsewhere on the board
/CAMERA/SCL0: Module1.80 (SCL0); also elsewhere on the board
/CAMERA/SDA0: Module1.82 (SDA0); also elsewhere on the board
/CM5-GPIO/CONSOLE_RXD: CONSOLE1.4, Module1.51 (GPIO15)
/CM5-GPIO/CONSOLE_TXD: CONSOLE1.5, Module1.55 (GPIO14)
/CM5-GPIO/GPIO06: Module1.30 (GPIO6); also elsewhere on the board
/CM5-GPIO/GPIO7: H1.2, Module1.37 (GPIO7)
/CM5-GPIO/GPIO8: H1.1, Module1.39 (GPIO8)
/CM5-GPIO/GPIO9: H1.4, Module1.40 (GPIO9)
/CM5-GPIO/GPIO10: H1.3, Module1.44 (GPIO10)
/CM5-GPIO/GPIO11: H1.6, Module1.38 (GPIO11)
/CM5-GPIO/GPIO12: H1.9, Module1.31 (GPIO12)
/CM5-GPIO/GPIO13: H1.10, Module1.28 (GPIO13)
/CM5-GPIO/GPIO16: Module1.29 (GPIO16); also elsewhere on the board
/CM5-GPIO/GPIO17: Module1.50 (GPIO17); also elsewhere on the board
/CM5-GPIO/GPIO22: H1.5, Module1.46 (GPIO22)
/CM5-GPIO/GPIO23: H1.8, Module1.47 (GPIO23)
/CM5-GPIO/GPIO24: H1.7, Module1.45 (GPIO24)
/CM5-GPIO/GPIO25: Module1.41 (GPIO25); also elsewhere on the board
/CM5-GPIO/GPIO26: Module1.24 (GPIO26); also elsewhere on the board
/CM5-GPIO/GPIO27: Module1.48 (GPIO27); also elsewhere on the board
/CM5-GPIO/I2S_DOUT: Module1.25 (GPIO21); also elsewhere on the board
/CM5-GPIO/PMIC_EN: Module1.99 (PMIC_ENABLE); also elsewhere on the board
/CM5-GPIO/RUN_PG: Module1.92 (PWR_BUT); also elsewhere on the board
/CM5-GPIO/SCL1: Module1.56 (GPIO3); also elsewhere on the board
/CM5-GPIO/SDA1: Module1.58 (GPIO2); also elsewhere on the board
/CM5-GPIO/SD_CLK: Module1.57 (SD_CLK), SDCARD2.5 (CLK)
/CM5-GPIO/SD_CMD: Module1.62 (SD_CMD), SDCARD2.3 (CMD)
/CM5-GPIO/SD_DAT0: Module1.63 (SD_DAT0), SDCARD2.7 (DAT0)
/CM5-GPIO/SD_DAT1: Module1.67 (SD_DAT1), SDCARD2.8 (DAT1)
/CM5-GPIO/SD_DAT2: Module1.69 (SD_DAT2), SDCARD2.1 (DAT2)
/CM5-GPIO/SD_DAT3: Module1.61 (SD_DAT3), SDCARD2.2 (CD/DAT3)
/CM5-GPIO/SD_PWR_ON: Module1.75 (SD_PWR_ON), R142.2, U6.4 (EN/EN#)
/CM5-GPIO/UART2_RX: Module1.34 (GPIO5); also elsewhere on the board
/CM5-GPIO/UART2_TX: Module1.54 (GPIO4); also elsewhere on the board
/SPEAKER-MIC/BCLK: Module1.49 (GPIO18); also elsewhere on the board
/SPEAKER-MIC/DOUT: Module1.27 (GPIO20); also elsewhere on the board
/SPEAKER-MIC/LRCLK: Module1.26 (GPIO19); also elsewhere on the board
GND: BOOT1.2, C1.2, C2.2, C3.2, C4.2, CONSOLE1.1, H1.12, Module1.1 (GND), Module1.2 (GND), Module1.7 (GND), Module1.8 (GND), Module1.13 (GND), Module1.14 (GND), Module1.22 (GND), Module1.23 (GND), Module1.32 (GND), Module1.33 (GND), Module1.42 (GND), Module1.43 (GND), Module1.52 (GND), Module1.53 (GND), Module1.59 (GND), Module1.60 (GND), Module1.65 (GND), Module1.66 (GND), Module1.71 (GND), Module1.74 (GND), Module1.98 (GND), Q10.2 (S), SDCARD2.6 (VSS), SDCARD2.9, SDCARD2.10, SDCARD2.11, SDCARD2.12, SDCARD2.13, SDCARD2.14, U6.2 (GND); also elsewhere on the board
unnamed: BOOT1.1, Module1.93 (nRPIBOOT)
unnamed: C2.1, Module1.88 (+1.8v_(Output)), Module1.90 (+1.8v_(Output))
unnamed: CM_ACT1.1 (A), R85.2
unnamed: CM_ACT1.2 (K), Module1.21 (LED_nACT)
unnamed: CM_PWR1.1 (A), R82.2
unnamed: CM_PWR1.2 (K), Q10.3 (D)
unnamed: Module1.95 (LED_nPWR), Q10.1 (G)
unnamed: C4.1, SDCARD2.4 (VDD), U6.1 (VOUT)
VCC3V3_M2: H1.11; also elsewhere on the board
VCC-5V-REG: C3.1, Module1.77 (+5v_(Input)), Module1.79 (+5v_(Input)), Module1.81 (+5v_(Input)), Module1.83 (+5v_(Input)), Module1.85 (+5v_(Input)), Module1.87 (+5v_(Input)); also elsewhere on the board

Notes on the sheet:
UART3_TX on the CM4
Compatible with TTL-234X-3V3 smart cable
UART3_RX on the CM4

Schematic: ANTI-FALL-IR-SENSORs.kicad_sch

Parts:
BUMP_CLIFF1: S16B-PHDSS_LF_SN; Manufacturer Part S16B-PHDSS(LF)(SN); LCSC C161675
Q5, Q6: 2302V; Manufacturer Part 2302V; LCSC C7431443
R30, R35: 330; R_0603_1608Metric
R38, R39, R41, R44: 10k; R_0603_1608Metric
R48, R53: 100k; R_0603_1608Metric

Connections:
/ANTI-FALL/ANTI-FALL-LEFT-DOWN-ADC: BUMP_CLIFF1.13, R41.1; also elsewhere on the board
/ANTI-FALL/ANTI-FALL-LEFT-UP-ADC: BUMP_CLIFF1.5, R38.1; also elsewhere on the board
/ANTI-FALL/ANTI-FALL-RIGHT-DOWN-ADC: BUMP_CLIFF1.14, R44.1; also elsewhere on the board
/ANTI-FALL/ANTI-FALL-RIGHT-UP-ADC: BUMP_CLIFF1.6, R39.1; also elsewhere on the board
/ANTI-FALL/BUMPER_LED_EN: Q5.1 (G), R53.1; also elsewhere on the board
/ANTI-FALL/CLIFF_LED_EN: Q6.1 (G), R48.1; also elsewhere on the board
/ANTI-FALL/L1-: BUMP_CLIFF1.1, Q5.3 (D)
/ANTI-FALL/LR-: BUMP_CLIFF1.15, Q6.3 (D)
/ANTI-FALL/R2+: BUMP_CLIFF1.2, R30.1
/ANTI-FALL/RR+: BUMP_CLIFF1.16, R35.1
GND: BUMP_CLIFF1.7, BUMP_CLIFF1.8, BUMP_CLIFF1.9, BUMP_CLIFF1.10, Q5.2 (S), Q6.2 (S), R38.2, R39.2, R41.2, R44.2, R48.2, R53.2; also elsewhere on the board
VCC-3V3-P: BUMP_CLIFF1.3, BUMP_CLIFF1.4, BUMP_CLIFF1.11, BUMP_CLIFF1.12; also elsewhere on the board
VCC-5V-REG: R30.2, R35.2; also elsewhere on the board

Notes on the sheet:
ANTI FALL SENSORs

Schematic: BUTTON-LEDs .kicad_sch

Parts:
HOME1: YLED0603B; Manufacturer Part YLED0603B; LCSC C19171394
PWR1: YLED0603B; Manufacturer Part YLED0603B; LCSC C19171394
R77, R78: 1k; R_0603_1608Metric
R120, R121: 1k; R_0603_1608Metric; VOLTAGERATE *; MANUFACTURINGPARTNUMBER *
SW1, SW2, SW3: TC-6601-5_0-260-8_3; Manufacturer Part TC-6601-5.0-260-8.3; LCSC C7528752

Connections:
/BUTTON-LED/CLEAN-BTN: R121.1, SW3.3, SW3.4; also elsewhere on the board
/BUTTON-LED/HOME-BTN: R120.1, SW2.3, SW2.4; also elsewhere on the board
/BUTTON-LED/LED-HOME: R77.1; also elsewhere on the board
/BUTTON-LED/LED-PWR: R78.1; also elsewhere on the board
/BUTTON-LED/POWER-BTN: SW1.3, SW1.4; also elsewhere on the board
GND: HOME1.2 (K), PWR1.2 (K), SW1.1, SW1.2, SW2.1, SW2.2, SW3.1, SW3.2; also elsewhere on the board
unnamed: HOME1.1 (A), R77.2
unnamed: PWR1.1 (A), R78.2
VCC-3V3-P: R120.2, R121.2; also elsewhere on the board

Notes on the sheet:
LEDs AND BUTTONs
